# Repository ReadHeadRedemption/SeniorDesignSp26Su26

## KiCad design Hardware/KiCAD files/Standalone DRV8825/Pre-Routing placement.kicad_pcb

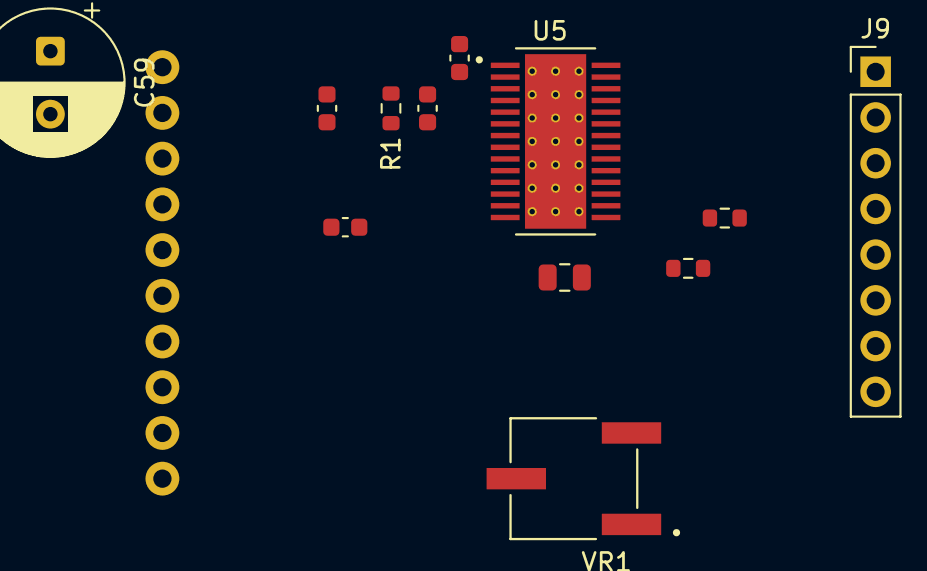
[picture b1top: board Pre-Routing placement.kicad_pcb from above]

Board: 2 copper layers, 13 parts (0 on the bottom side), 21 nets, no tracks yet.

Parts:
C1: 470nF; C_0805_2012Metric
C56: 10nF; C_0603_1608Metric
C57, C58, C60: 0.1uF; C_0603_1608Metric
C59: 100uF_50V; CP_Radial_D8.0mm_P3.50mm
J9: PINHD_1x8_Male; PinHeader_1x08_P2.54mm_Vertical
J17: Conn_01x10; 1x10_P2.54mm
R1: 1 Mohm; R_0603_1608Metric
R40: 1.5k; R_0603_1608Metric
R43: 10k; R_0603_1608Metric
U5: DRV8825PWPR; IC_TPS61196PWPRQ1
VR1: 3361P-1-104GLF; TRIM_3361P-1-104GLF

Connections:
+3V3: C1.1, U5.15 (V3P3OUT), VR1.3
+12V: C57.2, C58.1, C59.1, C60.1, J17.10, R1.1, U5.4 (VMA), U5.11 (VMB)
/A1: J9.3, U5.5 (AOUT1)
/A2: J9.4, U5.7 (AOUT2)
/B1: J9.2, U5.10 (BOUT1)
/B2: J9.1, U5.8 (BOUT2)
/Set Home: J17.4, U5.16 (NRESET)
GND: C1.2, C58.2, C59.2, C60.2, J9.5, J9.8, J17.9, U5.6 (ISENA), U5.9 (ISENB), U5.14 (GND), U5.28 (GND), VR1.1
unnamed: J9.6, R40.2, R43.1
unnamed: J17.1, U5.20 (DIR)
unnamed: J17.2, U5.22 (STEP)
unnamed: J17.5, U5.26 (MODE2)
unnamed: J17.6, U5.25 (MODE1)
unnamed: J17.7, U5.24 (MODE0)
unnamed: J17.8, U5.21 (NENBL)
unnamed: U5.12 (AVREF), U5.13 (BVREF), VR1.2
unnamed: C56.1, U5.1 (CP1)
unnamed: C56.2, U5.2 (CP2)
unnamed: R40.1, U5.18 (NFAULT)
unnamed: C57.1, R1.2, U5.3 (VCP)
SLP: J17.3, R43.2, U5.17 (NSLEEP)

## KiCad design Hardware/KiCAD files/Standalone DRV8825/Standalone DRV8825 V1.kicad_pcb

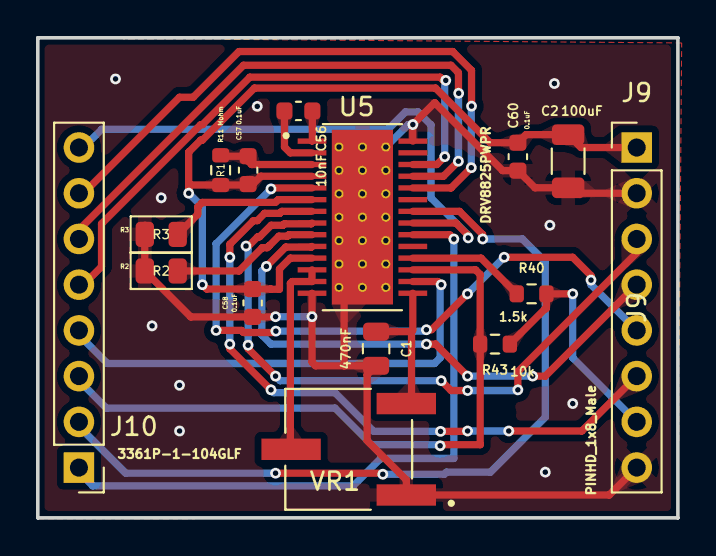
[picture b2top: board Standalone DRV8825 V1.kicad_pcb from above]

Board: 2 copper layers, 35.6 x 26.7 mm, 15 parts (0 on the bottom side), 23 nets.

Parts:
C1: 470nF; C_0805_2012Metric
C2: 100uF; C_1206_3216Metric
C56: 10nF; C_0603_1608Metric
C57, C58, C60: 0.1uF; C_0603_1608Metric
J9, J10: PINHD_1x8_Male; PinHeader_1x08_P2.54mm_Vertical
R1: 1 Mohm; R_0603_1608Metric
R2, R3: R_0805; R_0805_2012Metric
R40: 1.5k; R_0603_1608Metric
R43: 10k; R_0603_1608Metric
U5: DRV8825PWPR; IC_TPS61196PWPRQ1
VR1: 3361P-1-104GLF; TRIM_3361P-1-104GLF

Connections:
+3V3: C1.1, U5.15 (V3P3OUT), VR1.3
+12V: C2.1, C57.2, C58.1, C60.1, J9.1, R1.1, U5.4 (VMA), U5.11 (VMB)
/A1: J9.5, U5.5 (AOUT1)
/A2: J9.6, U5.7 (AOUT2)
/B1: J9.4, U5.10 (BOUT1)
/B2: J9.3, U5.8 (BOUT2)
GND: C1.2, C2.2, C58.2, C60.2, J9.2, J9.8, R2.2, R3.2, U5.14 (GND), U5.28 (GND), U5.29 (EPAD), VR1.1
unnamed: J9.7, R40.2, R43.1
unnamed: U5.12 (AVREF), U5.13 (BVREF), VR1.2
unnamed: C56.1, U5.1 (CP1)
unnamed: C56.2, U5.2 (CP2)
unnamed: J10.1, U5.20 (DIR)
unnamed: R3.1, U5.6 (ISENA)
unnamed: R2.1, U5.9 (ISENB)
unnamed: J10.7, U5.24 (MODE0)
unnamed: J10.6, U5.25 (MODE1)
unnamed: J10.5, U5.26 (MODE2)
unnamed: J10.8, U5.21 (NENBL)
unnamed: R40.1, U5.18 (NFAULT)
unnamed: J10.4, U5.16 (NRESET)
unnamed: J10.2, U5.22 (STEP)
unnamed: C57.1, R1.2, U5.3 (VCP)
SLP: J10.3, R43.2, U5.17 (NSLEEP)

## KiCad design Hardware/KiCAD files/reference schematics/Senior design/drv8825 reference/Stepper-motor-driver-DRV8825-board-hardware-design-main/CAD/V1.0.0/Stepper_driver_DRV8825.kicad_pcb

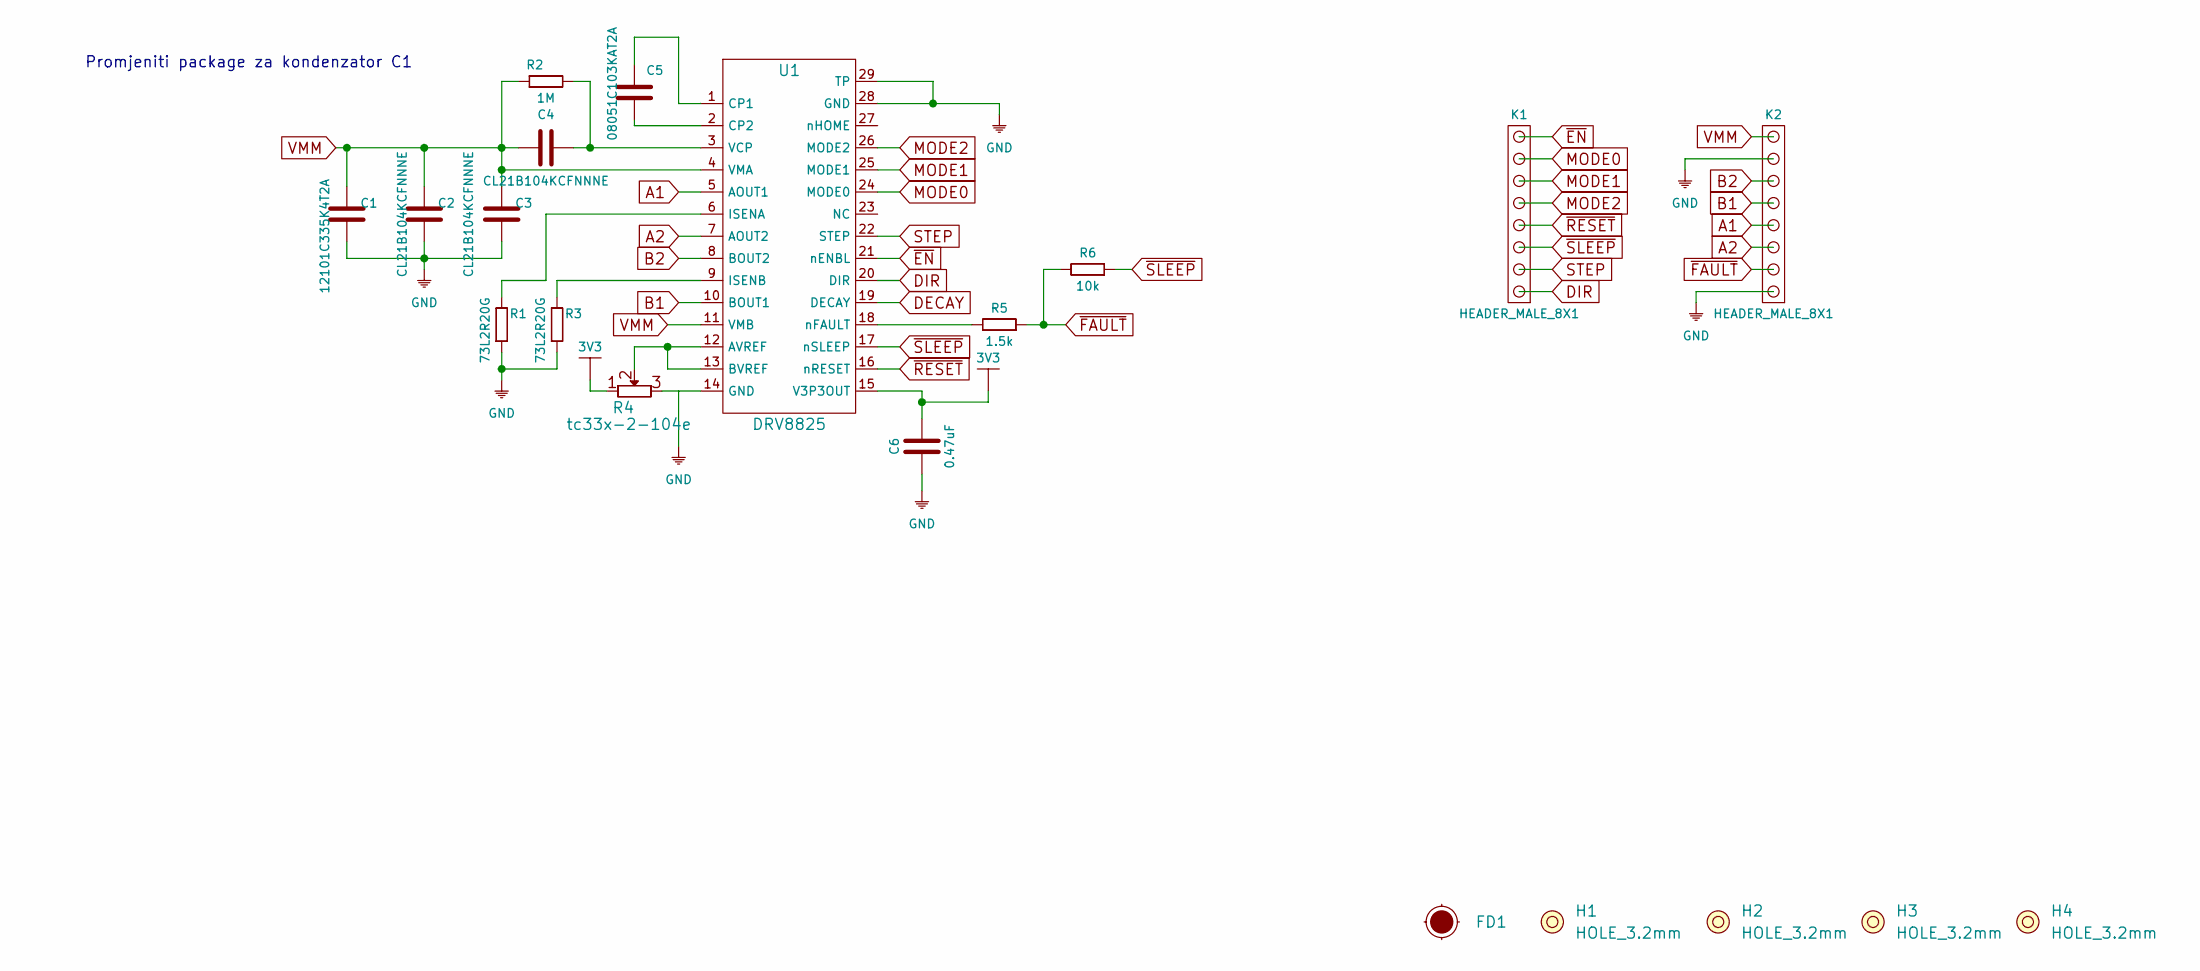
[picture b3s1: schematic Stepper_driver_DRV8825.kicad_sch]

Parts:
C1: 12101C335K4T2A; 0805C
C2, C3, C4: CL21B104KCFNNNE; 0805C
C5: 08051C103KAT2A; 0805C
C6: 0.47uF; 0603C
FD1: Fiducial_Stencil; FIDUCIAL_1MM_PASTE
H1, H2, H3, H4: HOLE_3.2mm
K1, K2: HEADER_MALE_8X1
R1, R3: 73L2R20G; 0603R
R2: 1M; 0603R
R4: tc33x-2-104e; tc33x-2-103e
R5: 1.5k; 0603R
R6: 10k; 0603R
U1: DRV8825

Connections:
3V3: C6.2, R4.1, U1.15 (V3P3OUT)
A1: K2.4, U1.5 (AOUT1)
A2: K2.3, U1.7 (AOUT2)
B1: K2.5, U1.10 (BOUT1)
B2: K2.6, U1.8 (BOUT2)
DECAY: U1.19 (DECAY)
DIR: K1.1, U1.20 (DIR)
GND: C1.1, C2.1, C3.1, C6.1, K2.1, K2.7, R1.1, R3.1, U1.14 (GND), U1.28 (GND), U1.29 (TP)
MODE0: K1.7, U1.24 (MODE0)
MODE1: K1.6, U1.25 (MODE1)
MODE2: K1.5, U1.26 (MODE2)
unnamed: C4.2, R2.2, U1.3 (VCP)
unnamed: C5.1, U1.2 (CP2)
unnamed: C5.2, U1.1 (CP1)
unnamed: R1.2, U1.6 (ISENA)
unnamed: R3.2, U1.9 (ISENB)
unnamed: R4.2, U1.12 (AVREF), U1.13 (BVREF)
unnamed: R5.2, U1.18 (nFAULT)
STEP: K1.2, U1.22 (STEP)
VMM: C1.2, C2.2, C3.2, C4.1, K2.8, R2.1, U1.4 (VMA), U1.11 (VMB)
~EN: K1.8, U1.21 (nENBL)
~FAULT: K2.2, R5.1, R6.2
~RESET: K1.4, U1.16 (nRESET)
~SLEEP: K1.3, R6.1, U1.17 (nSLEEP)

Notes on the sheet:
Promjeniti package za kondenzator C1

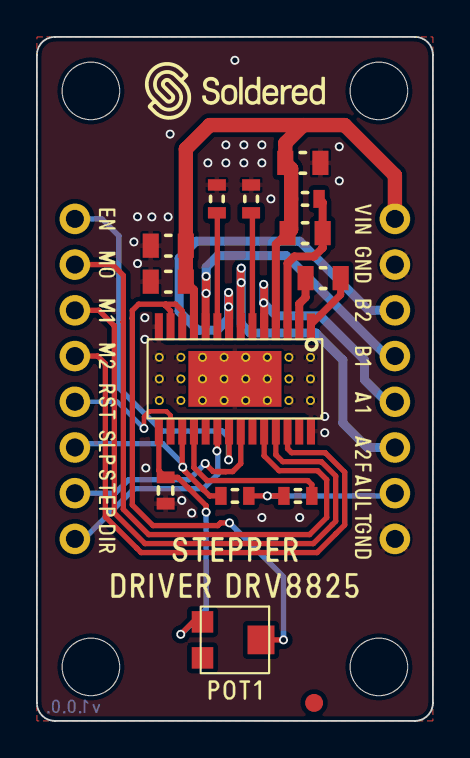
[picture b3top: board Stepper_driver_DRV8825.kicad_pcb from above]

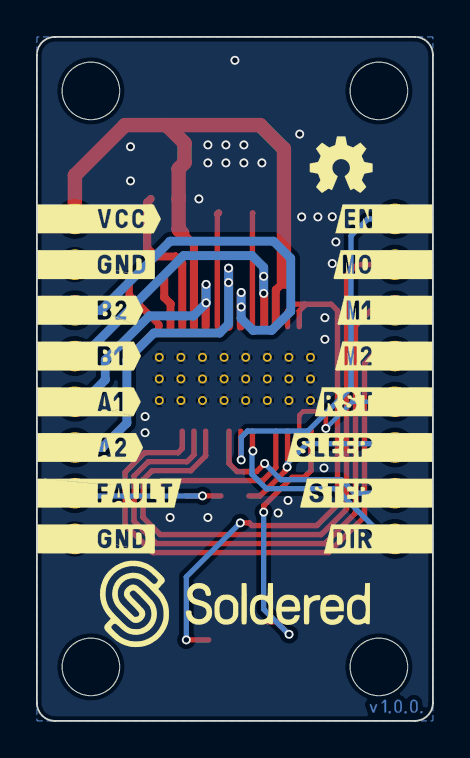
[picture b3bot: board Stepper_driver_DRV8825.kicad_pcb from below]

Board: 2 copper layers, 22.0 x 38.0 mm, 20 parts (2 on the bottom side), 23 nets.
